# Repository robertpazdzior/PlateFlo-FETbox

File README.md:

# PlateFlo FETbox - Hardware Controller
FETbox hardware controller for the PlateFlo plate-scale perfusion tissue culture
system.

See [publication](https://doi.org/10.1016/j.ohx.2021.e00222) and [ReadTheDocs](https://plateflo.readthedocs.io) for a detailed description of the whole
system and documentation of its components. 

## Description
Hosted here are all of the necessary files to build a FETbox hardware
controller. Source files are also included should you need to make 
modifications for your application.
* [Enclosure](./Enclosure/STLs)
    * [STLs]() - for 3D printing
    * [CAD](./Enclosure/CAD) - STEP and F3D complete device models
* [PCB](./PCB)
    * [JLCPCB](https://jlcpcb.com/) CAM files (for PCB ordering)
    * [EAGLE](https://www.autodesk.com/products/eagle/overview) `.SCH` and `.BRD` [source files](./PCB/EAGLE)
* Arduino Nano FETbox [firmware](./Firmware_FETbox)

## License
This project is copyright of Robert Pazdzior (2020-2021)

It is provided under the terms of the [CERN Open Hardware License
(CERN-OHL-W)](https://cern-ohl.web.cern.ch/home). A copy of the license is
included [here](LICENSE).

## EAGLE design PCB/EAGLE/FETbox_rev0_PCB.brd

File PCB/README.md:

# PCB
See [project documentation](https://plateflo.readthedocs.io/en/latest/hardware/build_guide.html#fetbox-hardware-controller) for manufacture and assembly guides.

## Files
File | Description
--- | ---
FETbox_rev0_Gerber_JLCPCB.zip | JLCPCB CAM (Gerber) files for production
EAGLE\FETbox_rev0_PCB.brd | EAGLE board
EAGLE\FETbox_rev0_PCB.sch | EAGLE schematic
EAGLE\\*.b#[0-9] | EAGLE routing support files
EAGLE\\*.pro | EAGLE auto-routing stats file
FETbox_rev0_schematic.pdf/dxf | Circuit diagram

## Overview

## Top

## Bottom

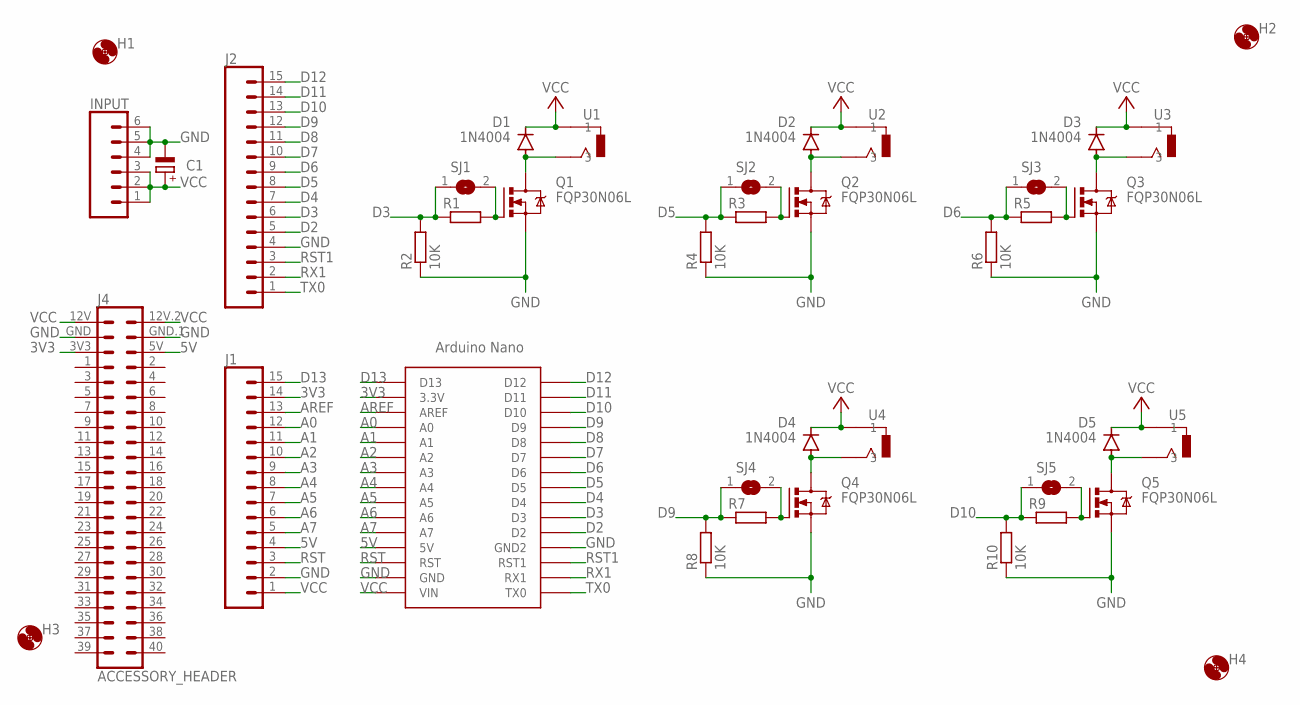
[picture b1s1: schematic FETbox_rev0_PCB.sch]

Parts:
C1: CPOL-EUE2.5-6; E2,5-6
D1, D2, D3, D4, D5: 1N4004; DO41-10
H1, H2, H3, H4: MOUNT-HOLE3.0; 3,0
INPUT: CONN_06LONGPADS; 1X06_LONGPADS
J1, J2: CONN_15; 1X15
J4: ACCESSORY_HEADER; 2X23
Q1, Q2, Q3, Q4, Q5: FQP30N06L; TO220
R1, R3, R5, R7, R9: 100; 0207/10
R2, R4, R6, R8, R10: 10K; 0207/10
SJ1, SJ2, SJ3, SJ4, SJ5: SJ
U1, U2, U3, U4, U5: CL13845G
U$2: NANO

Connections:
3V3: J1.14, J4.3V3, U$2.3.3V
5V: J1.4, J4.5V, U$2.5V
A0: J1.12, U$2.A0
A1: J1.11, U$2.A1
A2: J1.10, U$2.A2
A3: J1.9, U$2.A3
A4: J1.8, U$2.A4
A5: J1.7, U$2.A5
A6: J1.6, U$2.A6
A7: J1.5, U$2.A7
AREF: J1.13, U$2.AREF
D2: J2.5, U$2.D2
D3: J2.6, R1.1, R2.2, SJ1.1, U$2.D3
D4: J2.7, U$2.D4
D5: J2.8, R3.1, R4.2, SJ2.1, U$2.D5
D6: J2.9, R5.1, R6.2, SJ3.1, U$2.D6
D7: J2.10, U$2.D7
D8: J2.11, U$2.D8
D9: J2.12, R7.1, R8.2, SJ4.1, U$2.D9
D10: J2.13, R9.1, R10.2, SJ5.1, U$2.D10
D11: J2.14, U$2.D11
D12: J2.15, U$2.D12
D13: J1.15, U$2.D13
GND: C1.-, INPUT.4, INPUT.5, INPUT.6, J1.2, J2.4, J4.GND, J4.GND.1, Q1.S, Q2.S, Q3.S, Q4.S, Q5.S, R2.1, R4.1, R6.1, R8.1, R10.1, U$2.GND, U$2.GND1 (GND2)
unnamed: Q1.G, R1.2, SJ1.2
unnamed: D1.A, Q1.D, U1.S1 (3), U1.S2 (3)
unnamed: D2.A, Q2.D, U2.S1 (3), U2.S2 (3)
unnamed: Q2.G, R3.2, SJ2.2
unnamed: D3.A, Q3.D, U3.S1 (3), U3.S2 (3)
unnamed: Q3.G, R5.2, SJ3.2
unnamed: D4.A, Q4.D, U4.S1 (3), U4.S2 (3)
unnamed: Q4.G, R7.2, SJ4.2
unnamed: D5.A, Q5.D, U5.S1 (3), U5.S2 (3)
unnamed: Q5.G, R9.2, SJ5.2
RST: J1.3, U$2.RST
RST1: J2.3, U$2.RST1
RX1: J2.2, U$2.RX1
TX0: J2.1, U$2.TX0
VCC: C1.+, D1.C, D2.C, D3.C, D4.C, D5.C, INPUT.1, INPUT.2, INPUT.3, J1.1, J4.12V, J4.12V.2 (12V.1), U1.T1 (1), U1.T2 (1), U2.T1 (1), U2.T2 (1), U3.T1 (1), U3.T2 (1), U4.T1 (1), U4.T2 (1), U5.T1 (1), U5.T2 (1), U$2.RAW (VIN)

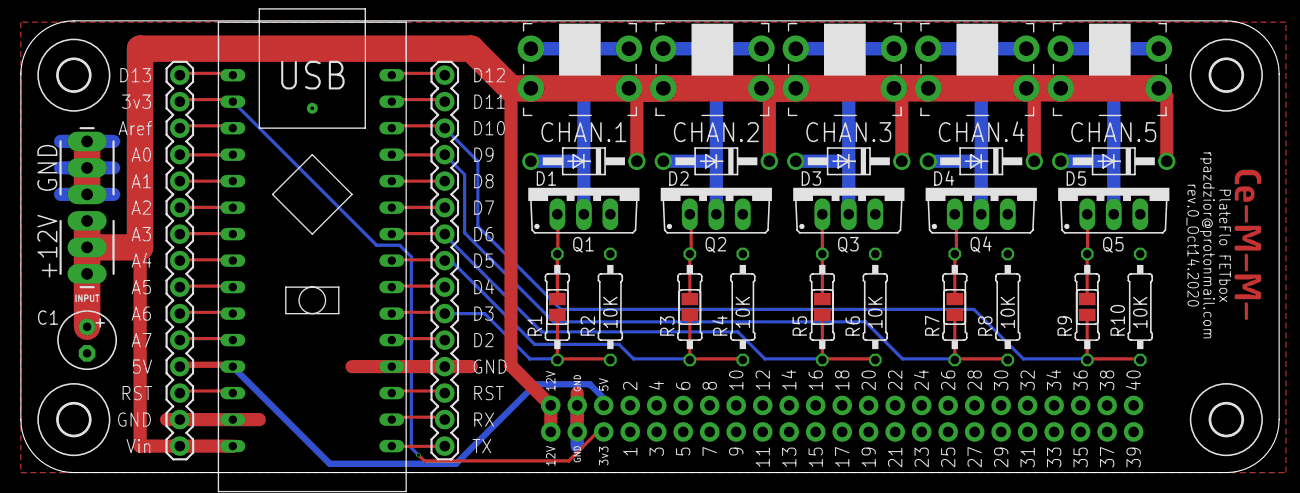
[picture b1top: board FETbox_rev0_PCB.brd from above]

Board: 2 copper layers, 120.6 x 43.3 mm, 40 parts (0 on the bottom side), 39 nets.

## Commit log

2021-02-04 files, images, markdowns
2021-02-04 rename .md files to README for GitHub
2021-02-04 STL link fixed
2021-02-04 enclosure img link
2021-02-04 ID command update
2021-03-10 sketch improved, fetbox lid, schematics
2021-04-14 docs links, file descriptions
2023-09-16 Update link to HardwareX publication

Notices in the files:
parts and their libraries:
SparkFun-Connectors: Licensing: Creative Commons ShareAlike 4.0 International - https://creativecommons.org/licenses/by-sa/4.0
